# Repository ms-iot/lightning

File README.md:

# **Microsoft.IoT.Lightning Nuget package**

This repository is for generating the Microsoft.IoT.Lightning Nuget package. This package contains code which is compiled into an application deployed to a board running Microsoft Windows IoT Core.

Also, the nuget package is periodically published to nuget.org. For more information on installing the published nuget package, please refer to [https://www.nuget.org/packages/Microsoft.IoT.Lightning/](https://www.nuget.org/packages/Microsoft.IoT.Lightning/)

This project has adopted the [Microsoft Open Source Code of Conduct](http://microsoft.github.io/codeofconduct). For more information see the [Code of Conduct FAQ](http://microsoft.github.io/codeofconduct/faq.md) or contact [opencode@microsoft.com](mailto:opencode@microsoft.com) with any additional questions or comments. 

## Build the Nuget package
- nuget.exe is required to build the Nuget package, so please download the Nuget command line utility [nuget.exe](http://nuget.org/nuget.exe) and make sure it's in the PATH. 
- Visual Studio 2017 is also required to build the sources ([Visual Studio Downloads](https://www.visualstudio.com/downloads/))
- Clone or download this repository
- Assuming F:\Github\lightning is your local repo root folder and all prerequisites above are met, run this command to both build the sources and create the Nuget package.

~~~
F:\Github\lightning>build.cmd
~~~

- Alternatively, if the sources are already built, run this command from the <root>\Nuget folder to create the Nuget package only.
  
~~~
F:\Github\lightning\Nuget>build-nupkg.cmd
~~~

### Set Nuget package source location

In order to install Nuget packages from your local builds, you'll need to add the folder where the Nuget package has been created (or copied) to the list of nuget package manager sources in Visual Studio. Following the below instructions for each sdk source:

In Visual Studio 2017, nativate to *Tools -> Library Package Manager -> Package Manager Settings*

1. Click the "+" button to add a new source
1. Set the name to something descriptive
1. Click the "..." button and navigate to your local folder where the Nuget package has been created; e.g. *F:\Github\lightning\Nuget*
1. Click the "Update" button to save the Package Sources changes

### Including prerelease Lightning packages

In order to install the latest prerelease version of Lightning as well as receive prerelease updates to the Lightning package, make sure to set the "Include prerelease" option in the Nuget Package Manager.

1. Right click References in your project
1. Click "Manager Nuget Packages..."
1. Select package sources for Lightning nuget
1. Click "Include prerelease".
1. Click "Install" to install the nuget package to your project

### Add required UWP Extensions

The IOT and Desktop UWP SDK Extensions are both required for building Lightning applications.

1. Right click "References" in your Visual C++ UWP Project
1. Choose "Add Reference..."
1. Open Universal Windows | Extensions
1. Choose Both "Windows Desktop Extensions for the UWP" and "Windows IoT Extensions for the UWP".

### Update Application Package manifest

Also, you need to update the Application Package manifest manually to reference the Lightning device interface.

1. Right click "Package.appxmanifest" in your Visual C++ UWP Project
2. Click "Open With.."
3. In the "Open With" dialog box, choose XML (Text) Editor and click OK
4. Edit the the Capabilities section in your application to add the following:
```XML
<iot:Capability Name="lowLevelDevices" />
<DeviceCapability Name="109b86ad-f53d-4b76-aa5f-821e2ddf2141"/>
```
5. The first is a capability that will enable the application to access custom devices.
6. The second is the device guid id for the Lightning interface
7. Save the file

Build your project to verify all prerequisites to use Lightning were successfully added.

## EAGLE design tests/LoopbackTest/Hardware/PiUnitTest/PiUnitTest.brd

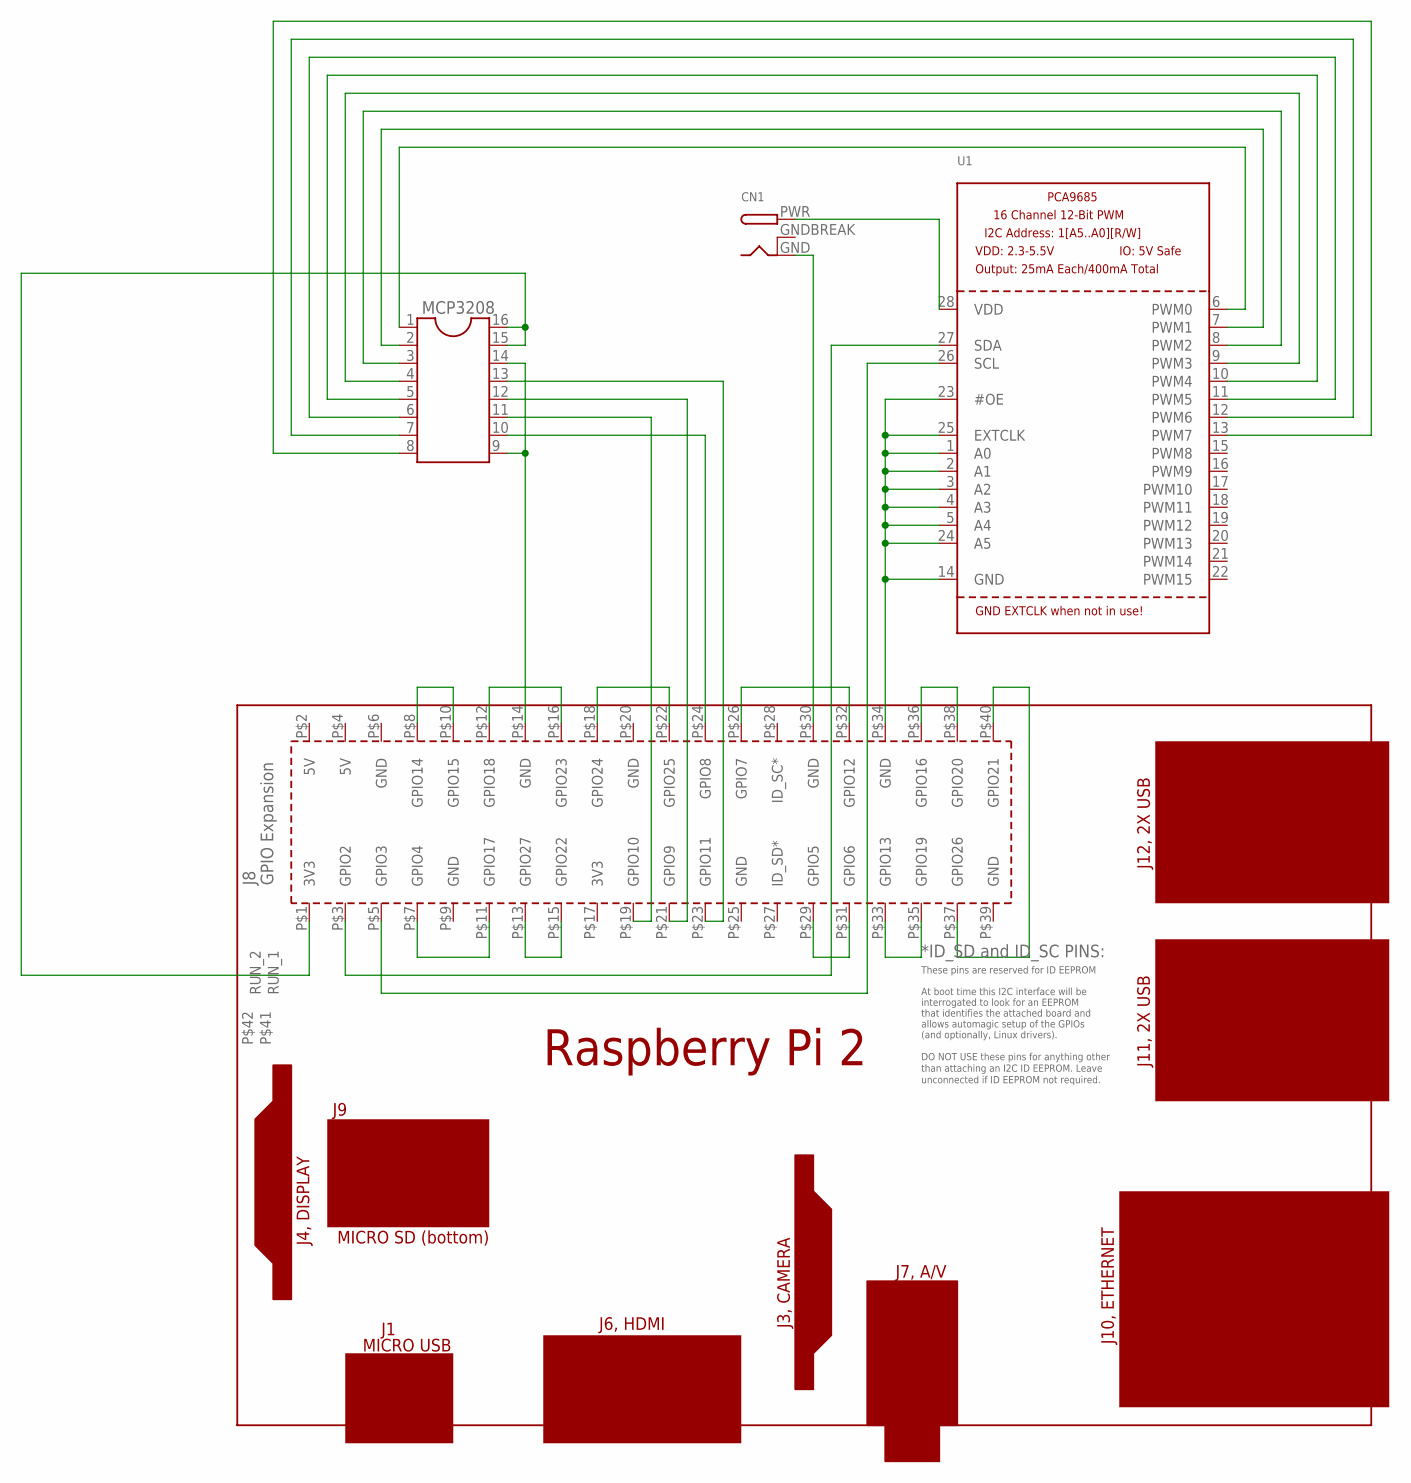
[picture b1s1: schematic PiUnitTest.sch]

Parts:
CN1: DCBARRELPTH; DCJACK_2MM_PTH
MCP3208: DIL16
PCB1: RPI2
U1: PCA9685; TSSOP28

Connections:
GNDBREAK: CN1.GNDBREAK
unnamed: CN1.GND, PCB1.P$30 (GND)
unnamed: MCP3208.9, MCP3208.14, PCB1.P$14 (GND)
unnamed: PCB1.P$34 (GND), U1.1 (A0), U1.2 (A1), U1.3 (A2), U1.4 (A3), U1.5 (A4), U1.14 (GND), U1.23 (#OE), U1.24 (A5), U1.25 (EXTCLK)
unnamed: MCP3208.15, MCP3208.16, PCB1.P$1 (3V3)
unnamed: MCP3208.13, PCB1.P$23 (GPIO11)
unnamed: MCP3208.12, PCB1.P$21 (GPIO9)
unnamed: MCP3208.11, PCB1.P$19 (GPIO10)
unnamed: MCP3208.10, PCB1.P$24 (GPIO8)
unnamed: CN1.PWR, U1.28 (VDD)
unnamed: PCB1.P$3 (GPIO2), U1.27 (SDA)
unnamed: PCB1.P$5 (GPIO3), U1.26 (SCL)
unnamed: MCP3208.1, U1.6 (PWM0)
unnamed: MCP3208.2, U1.7 (PWM1)
unnamed: MCP3208.3, U1.8 (PWM2)
unnamed: MCP3208.4, U1.9 (PWM3)
unnamed: MCP3208.5, U1.10 (PWM4)
unnamed: MCP3208.6, U1.11 (PWM5)
unnamed: MCP3208.7, U1.12 (PWM6)
unnamed: MCP3208.8, U1.13 (PWM7)
unnamed: PCB1.P$7 (GPIO4), PCB1.P$11 (GPIO17)
unnamed: PCB1.P$13 (GPIO27), PCB1.P$15 (GPIO22)
unnamed: PCB1.P$29 (GPIO5), PCB1.P$31 (GPIO6)
unnamed: PCB1.P$33 (GPIO13), PCB1.P$35 (GPIO19)
unnamed: PCB1.P$37 (GPIO26), PCB1.P$40 (GPIO21)
unnamed: PCB1.P$36 (GPIO16), PCB1.P$38 (GPIO20)
unnamed: PCB1.P$26 (GPIO7), PCB1.P$32 (GPIO12)
unnamed: PCB1.P$18 (GPIO24), PCB1.P$22 (GPIO25)
unnamed: PCB1.P$12 (GPIO18), PCB1.P$16 (GPIO23)
unnamed: PCB1.P$8 (GPIO14), PCB1.P$10 (GPIO15)

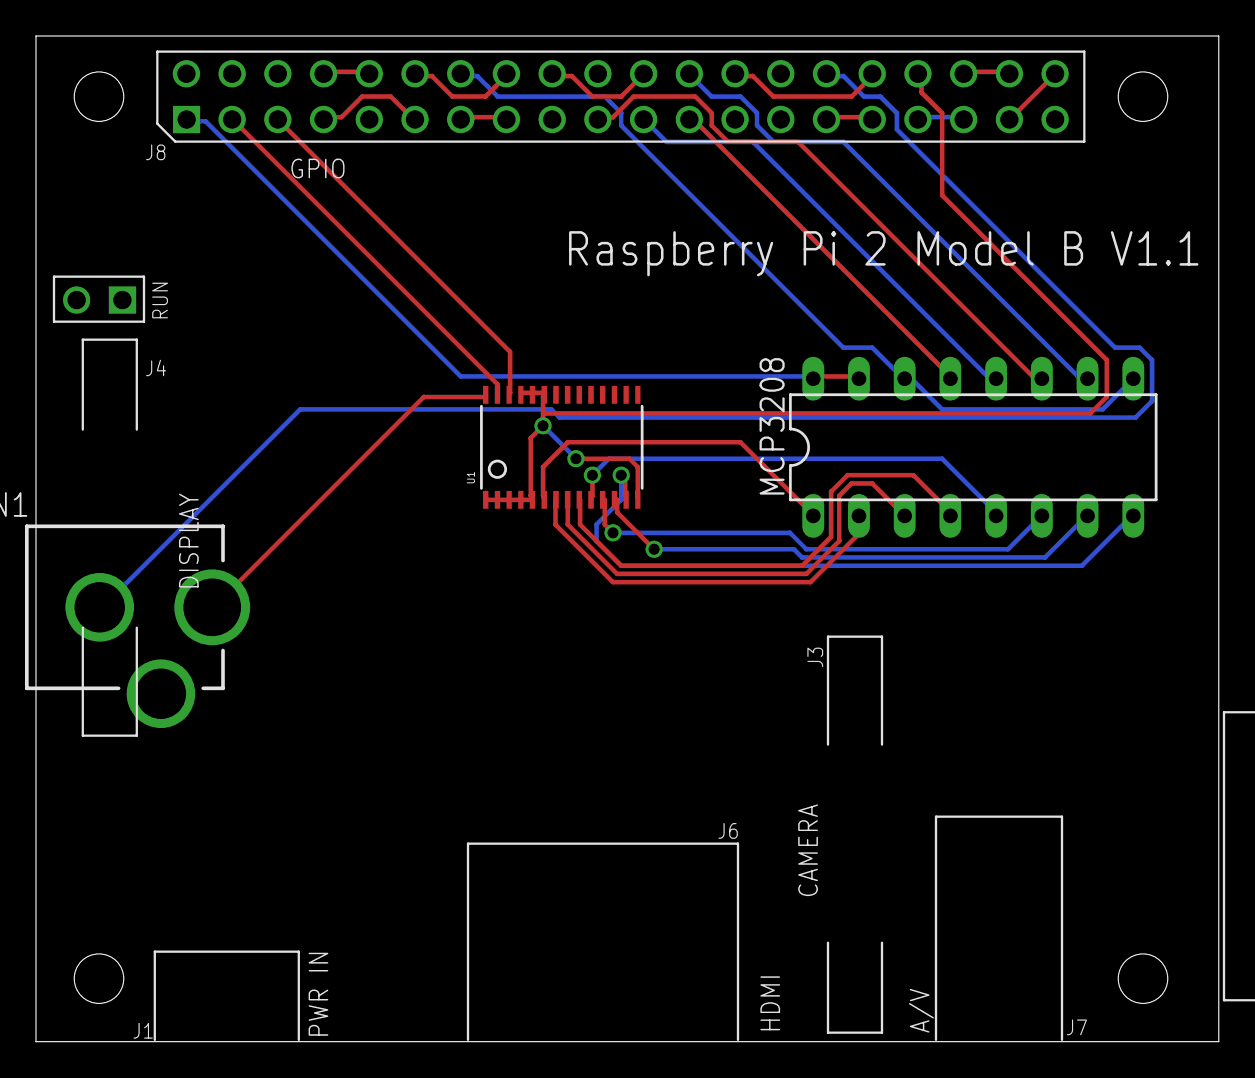
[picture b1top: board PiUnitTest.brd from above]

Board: 2 copper layers, 65.7 x 55.9 mm, 4 parts (0 on the bottom side), 29 nets.

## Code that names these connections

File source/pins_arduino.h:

// Copyright (c) Microsoft Open Technologies, Inc.  All rights reserved.  
// Licensed under the BSD 2-Clause License.  
// See License.txt in the project root for license information.

#ifndef _PINS_ARDUINO_H_
#define _PINS_ARDUINO_H_


#if defined(_M_IX86) || defined(_M_X64)

// Pin numbers mappings for MinnowBoard Max

const static uint8_t GPIO0 = 21;
const static uint8_t GPIO1 = 23;
const static uint8_t GPIO2 = 25;
const static uint8_t GPIO3 = 14;
const static uint8_t GPIO4 = 16;
const static uint8_t GPIO5 = 18;
const static uint8_t GPIO6 = 20;
const static uint8_t GPIO7 = 22;
const static uint8_t GPIO8 = 24;
const static uint8_t GPIO9 = 26;
const static uint8_t SCL = 13;
const static uint8_t SDA = 15;
const static uint8_t CS0 = 5;
const static uint8_t CE0 = CS0;
static const uint8_t SS = CS0;
const static uint8_t MISO = 7;
const static uint8_t MOSI = 9;
const static uint8_t SCLK = 11;
const static uint8_t SCK = SCLK;
const static uint8_t CTS1 = 10;
const static uint8_t RTS1 = 12;
const static uint8_t RX1 = 8;
const static uint8_t TX1 = 6;
const static uint8_t RX2 = 19;
const static uint8_t TX2 = 17;

#elif defined (_M_ARM)

// Pin numbers mappings for Raspberry Pi2

const static uint8_t GPIO2 = 3;
const static uint8_t GPIO3 = 5;
const static uint8_t GPIO4 = 7;
const static uint8_t GPIO5 = 29;
const static uint8_t GPIO6 = 31;
const static uint8_t GPIO7 = 26;
const static uint8_t GPIO8 = 24;
const static uint8_t GPIO9 = 21;
const static uint8_t GPIO10 = 19;
const static uint8_t GPIO11 = 23;
const static uint8_t GPIO12 = 32;
const static uint8_t GPIO13 = 33;
const static uint8_t GPIO14 = 8;
const static uint8_t GPIO15 = 10;
const static uint8_t GPIO16 = 36;
const static uint8_t GPIO17 = 11;
const static uint8_t GPIO18 = 12;
const static uint8_t GPIO19 = 35;
const static uint8_t GPIO20 = 38;
const static uint8_t GPIO21 = 40;
const static uint8_t GPIO22 = 15;
const static uint8_t GPIO23 = 16;
const static uint8_t GPIO24 = 18;
const static uint8_t GPIO25 = 22;
const static uint8_t GPIO26 = 37;
const static uint8_t GPIO27 = 13;
const static uint8_t GPIO47 = 41;
const static uint8_t GCLK = 7;
const static uint8_t GEN0 = 11;
const static uint8_t GEN1 = 12;
const static uint8_t GEN2 = 13;
const static uint8_t GEN3 = 15;
const static uint8_t GEN4 = 16;
const static uint8_t GEN5 = 18;
const static uint8_t SCL1 = 5;
const static uint8_t SDA1 = 3;
const static uint8_t CS0 = 24;
const static uint8_t CE0 = CS0;
static const uint8_t SS = CS0;
const static uint8_t CS1 = 26;
const static uint8_t CE1 = CS1;
const static uint8_t SCLK = 23;
const static uint8_t SCK = SCLK;
const static uint8_t MISO = 21;
const static uint8_t MOSI = 19;
const static uint8_t RXD = 10;
const static uint8_t TXD = 8;

static const uint8_t LED_BUILTIN = 41;

#endif // defined (_M_ARM)

#endif // _PINS_ARDUINO_H_

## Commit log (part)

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2014-06-23 Update read me
2014-06-23 Initial commit of the IoT Nuget Package for Intel Galileo
2014-06-26 Remove file
2014-06-28 License file
2014-07-02 Commit version
2014-07-17 Implemented native Arduino String class (WString)
2014-07-17 ifdef around Winsock headers to prevent collisions in the normal case
2014-07-19 Took the tabs out. Fixed splat from inlined initialization routines. Fixed a couple of pin initization of bugs.
2014-07-19 Fix pinMode() exception when pin set to PWM.
2014-07-19 Allow A0-A5 to be used to select analogRead(), digitalWrite(), or digitalRead() pins.
2014-07-21 Removing makeWord(unsigned int) - no workaround is required "word(unsigned int)" already works from word type (unsigned short) constructor IMPACT: minimizes the delta from the original Arduino API
2014-07-23 Rename pinFunction to _PinFunction This follows the internal function naming convention instead of the standard wiring naming convention
2014-07-24 Fix hardware serial, add word
2014-07-24 Added PrintTests to test folder
2014-07-24 Added Nuget Images
2014-07-24 Fixed the charset errors with apostrophe
2014-07-25 Fixed the DigitalPin tests to use the latest SDK NuGet
2014-07-25 Fixes NetworkSerial available and read methods.
2014-07-30 Add Servo stub, fix Hardware serial to use Stream as a base class
2014-08-01 Finally pushing changes for M1.2 MSI: 1) Updated template app to include HelloBlinky source 2) Changed project guid to be unique per-project using $guid1 macro 3) Removing nuget package from template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
2014-08-05 Implementation of pulseIn
2014-08-05 Improve readability by using branching instructions. Removing checks of binary parameter.
2014-08-07 Fix compiler warnings /W4
2014-08-11 PulsIn Test
2014-08-11 Don't use alpha NuGet for tests
2014-08-20 Stripping out pgmspace macros
2014-08-28 Implemented HardwareSerial and Tests
2014-09-02 Implemented analogReference() for Galileo (stubbed out) - provides runtime error to warn developers - Supplied doxygen formatted comments Made analogReadResolution() parameter const.
2014-09-05 Don't depend on a specific sdk version
2014-09-05 Fixup test suites
2014-09-05 Add multi-process support for Win32 I2C.
2014-09-05 Implemented I2C callbacks to allow read-modify-write transactions. Removed some I2C delays.
2014-09-09 Add ability to change network serial port
2014-09-09 Made Tone functions in Arduino.h and started ToneTest Project
2014-09-09 Updated Tone(duration) function to work with SetWaitableTimers and changed the toneRunningOnPin to work with static functions
2014-09-09 Changed tone based on review feedback Changed function documentation to doxygen Closed handle as well as canceled waitable timer Removed unused variables Added one more test
2014-09-10 Squashed pin initialization bug - "modeSet" attribute of "pinData" struct needed a default configuration instead of being initialized directly from GPIO chip - "modeSet" is updated every time pinMode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
2014-09-12 add missing file
2014-09-12 Fix typo
2014-09-15 Add analogWriteResolution() functional test to tests folder
2014-09-17 Implemented general GPIO support across all types of pins. Added support for aborting I2C transfers via callback. Implemented driving PWM chip as an I/O expander (for driving MUX select lines). Imple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
2014-09-24 Preliminary Implementation of Servo Library that uses PWM Start and Stop
2014-09-24 Implement Lightning nuget This change implements the lightning nuget. It also fixes an API compatibility bug.
2014-09-24 Removed Logging and added documentation around functions
2014-09-25 Implemented EEPROM
2014-09-25 missed forward declaration in wire.h
2014-09-26 Set I2C fast speed to 400khz.
2014-09-29 Add SetBitOrder to SPI
2014-09-29 Fixed inconsistent tab/spacing
2014-09-30 Fixes the multiple inclusion issue with Print.h when LiquidCrystal Library is used
2014-10-01 Added degrees() and radians() functions provided by the standard Arduino.h
2014-10-02 Fixed Hardware Serial from dropping null characters
2014-10-07 Implement analogReadResolution(). Added analogReadResolution() to set the number of bits returned from an ADC conversion. Scale ADC values to the requested number of bits in the analogRead() routine.
2014-10-10 Implemented analogWrite()/PWM for Gen2. Moved ADC pin number to channel translation out of the Arduino Wiring layer for simplicity and consistency. Fixed problem with pin attributes table from the I/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
2014-10-15 Fix for the char and string conversion compile errors present
2014-10-16 fix compilier warnings for radians() and float()
2014-10-16 Resolved several /W4 warnings
2014-10-16 Fixes to support compatibility
2014-10-16 Update dependency name
2014-10-16 Update readme for SDKFromArduino dependency
2014-10-16 Fix source highlight
2014-10-17 Added API Test Project for testing/calling global functions - provided valid NuGet package ids for eepromTest and analogWriteResolutionTest
2014-10-22 analogRead() for Gen1.
2014-10-24 Removing binary.h from galileo-sdk in favor of binary.h in arduino-sdk - this commit depends on arduino-sdk commit to not break the project - test added to API test solution
2014-10-25 Fix problem configuring Digital I/O pins.
2014-10-28 Removed extra I2C execute action from CY8 SetPinDirection(). Added 31.25 khz SPI clock speed for MIDI use.
2014-10-29 Lightning integration This change fixes up the last build artifacts from integration with the dmap branch. Renamed files with extra letters Fixed Servo's internal use of PWM (although lost frequency 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
2014-10-30 Fixup Network serial and Add Lean and mean
2014-11-08 Fix problem with chained I2C transfers in TwoWire. Reset I2C transaction after it is executed so it can be reused safely with the same I2C address.
2014-11-25 Make digitalRead return LOW on failure
2014-12-03 Support GPIO operations on the MBM "slow expansion" (26 pin) connector. Added attributes tables for MBM. Added logic to route GPIO read and write calls for MBM. Added logic to drive the BayTrail GPIO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
2014-12-19 SPI support for MinnowBoard Max. Implement basic SPI signals (MOSI, MISO, CLK) on the 26-pin connector.
2015-01-27 Cleanup things found during Ika Lure GPIO and PWM testing. Remove SOC pad pull-ups when configured as GPIO inputs. Remove unneeded variable in arduino.h.
2015-02-04 NuGet package support for MBM Ika Lure code. Removed tabs from source files.
2015-06-04 Use HRESULTs for error handling - 2
2015-07-02 User-mode code to work around no global mutex in UWP app. Conditionally compiled out some Galileo code from UWP build. Added formatting of Arduino errors in UWP.
2015-08-13 Initial changes to support Pi2. Included conditional compilation for ARM builds. Pi2 GPIO support (based on connector Pin numbers). Pi2 SPI support. Refactored SPI code into separate files for each t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
2015-09-24 Address code review comments.
2015-09-28 PI2 SPI fixes. Multi-byte reads were not recombined correctly. 24-bit reads were masked incorrectly to 16-bits.
2015-10-03 Rename nuget package to Microsoft.IoT.Lightning
    This change removes the obsolete nuspec and targets files, and adds a
    new set for Lightning nuget package. It has the name
    Microsoft.Iot.Lightning and version 1.0.0 with a dependency on Arduino
    SDK v1.0.1
2015-10-03 Revert "Revert "Rename nuget package to Microsoft.IoT.Lightning""
    This reverts commit e6285a5c3f47d832495d054be9c745d9d7369ab3.
2015-10-05 Add missing SPI sources to nuget package
2015-10-05 Add new methods to BoardPinsClass to be used by the DmapProvider
    The new method, mapIfNeeded, allow the GPIO controller classes to not be
    lazy init'ed. The getGpioPinCount is needed by the GPIO Device provider
    to get the number of pins.
2015-10-05 Make version prerelease (version number is now 1.0.0-beta)
2015-10-05 Update docs and images
2015-10-05 Update Readme to fix image links
2015-10-05 Add png file for docs
2015-10-06 Update README.md
    Fixed a small typo: lighning to lightning
2015-10-06 Update README.md to include dependency on Arduino-SDK
2015-10-07 Add back SPI consts in ArduinoCommojn.h that were erroneously removed by previous commit
2015-10-07 Fix build issues when ErrorCodes.h is included in a source before std::map is declared
2015-10-08 Add hex decimal values for error codes
2015-10-09 Remove the dependencies on task.get() and task.wait() which allow the API to be useable in the UI thread
    Additionally, added synchronization to GpioController initialization
    paths since the API can be used from multiple threads when the global
    variables are used.
    TODO: Check if similar synchronization need to be added to other
    controllers initialization.
2015-10-10 Remove locks from GPIO Controller and driver initialization path
2015-10-14 Fix pinMode() clobbering I2C, etc. Set pin to Digital I/O when pinMode() is called on it, verifying the pin is not already locked for another use
2015-10-15 Add LED_BUILTIN name
2015-10-29 Remove TODOs from dmapsupport
    Also, promptly return on failures
2015-11-06 Move forward to Arduino 1.6.6
2015-11-06 Update comments
2015-11-13 removed PWM_MAX_DUTYCYCLE define which was used for Arduino internal logic, but not used in our implementation
    this value can cause confusion when working with PWM as it is not valid for any real value.
2015-11-20 Hardware Serial support.
2015-11-20 Remove TODOs.
2015-11-21 Fix typo in comment.
2015-12-11 Remove Galileo specific code.
2015-12-11 Add some comments to ADC
2015-12-11 Correct app manifest
2016-01-27 Hardware interrupt support for PI2 and MBM.
2016-02-11 Allow 64-bits for address from driver.
2016-03-07 Fix #30
    This fixes the exception you get when trying to use I2C in shared mode. There may be other implications by moving this from Exclusive to Shared but testing has not surfaced any issues.
2016-03-07 Fix I2c bus clock divider and misc cleanup
    The clock divider for the i2c controller on RPI2 was not adjusted to the
    RPI2 clock speed. So, fixes it for both high and normal speed.
    Additionally, there are miscellaneous code cleanup for various sources.
2016-03-25 Update DMAP support to match driver headers
    The DMAP driver now uses native* on ARM, x32 and x64, for its user mode
    memory mapped address. So, update Lightning to use the same.
    Additionally, this change changes the nuget package version to v1.0.3
    (removing prerelease).
2016-04-12 Update version number for Nuget
2016-05-11 Build required changes
2016-06-03 Update Nuget version
    Also, remove unused file
2016-06-28 Add Arduino Wiring basic test suite
2016-06-29 Updated Arduino pins for MBM
2016-06-30 Move debug print to Print class
    Ensure only Serial.print and Serial.println need to print to the output
    debug.
2016-07-12 Provider's GPIO pin drive mode defaults to output
    Some samples/test code don't out of the box work on MBM when the GPIO
    pin drive mode is not pre-initialized to output, so set that as the
    default.
2016-07-12 Optimizing drive mode
    Needed to improve compatibility with demos
2016-07-15 Add nuspec for public publishing
2016-08-11 Support SPI1 controller on RPI
    Enables the SPIClass (SPI) users to select between SPI0 and SPI0
    controllers using a new overload for SPI.begin(). Sketches using the
    original SPI.begin() will default to SPI0.
2017-02-28 fix an issue with HardwareSerial destructor
2018-02-13 Fix Lightning GPIO interrupts on MBM platforms. Add BoardType member to LightningGpioPinProvider for use in s_interruptCallback. We need to check the board type in the interrupt callback because the 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
2018-02-13 Add error checking for _BoardType
2018-02-13 Revert "Better initialization for BoardType"
    This reverts commit 6cf90d0b11d9e5ba25a94b541c0366d822a612fd.
